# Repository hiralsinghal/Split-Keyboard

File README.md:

# Split-Keyboard
A split-keyboard made for ergnomic comfort. It has 42 keys, each side having 21. XIAO-nRF5280 is the MCU powering the project because of its wireless support.

## Features

- Wireless
- XIAO-nRF52840 is the MCU.
- 42 keys

## Schematic

You have draw hierarchical sheets and set the sheetname respectly whereas the sheet file should be named the same for both so that whatever symbols you place in one of them are copied into the other without you switching sheets constantly. This wouldnt impact the way footprints are imported into the PCB editor.

### Left Side

### Right Side

## PCB

The source files are in the PCB folder.

## Case

This was made in Fusion, using the PCB as reference. It has cutouts for switches, keys and XIAO ports. The source file can be found in the folder CAD.

### Left

This is the case for the left side of the keyboard.

### Right

This is the case for the right side of the keyboard.

## Firmware

It uses ZMK firmware because of its support for split keyboards. Each controller runs their own firmware but they make it work as a single device. The files are in the firmware folder.

## BOM

| Item | Description | Quantity | Unit Price ($) | Total Price ($) | URL |
| --- | --- |---| --- |--- | --- |
| PCB | PCB | 5 | 3.32 | 16.6 | |
| Seeed Studio XIAO BLE nRF52840 |MCU |2|12.2|24.4|https://robu.in/product/seeed-studio-xiao-ble-nrf52840/ |
| Akko V3 Lavender Purple Pro Switch (Pack of 45)| Keyboard Switches | 1 | 11.65 | 11.65 | https://stackskb.com/store/akko-v3-lavender-purple-pro-switch-pack-of-45/ |
| Veekos Gradient Keycaps (Cherry Profile) (135 keys)| Keycaps | 1 | 13.77 | 13.77 | https://stackskb.com/store/veekos-gradient-keycaps-cherry-profile-135-keys/?attribute_pa_colour=black |
| 1N5819 1W Diode | Diode | 42 | 0.027 | 1.13 | https://robu.in/product/1n5819-1w-diode-pack-of-30/ |
| 0805S8F1005T5E-Royal Ohm-10M 1% 0805 SMD Resistor | Resistor | 4 | 0.0086 | 0.034 | https://robu.in/product/0805s8f1005t5e-royal-ohm-10m-1-0805-smd-resistor/
| Total | | | |67.584| |

## Zine

This was made in Figma. I enjoyed making it kinda.

## Why did I make it?

I made it cause it seemed like a cool project. The routing was tough ngl. Each footprint alligned differently and so many switches and diodes. Its like each project is improving my skills consistently. I now know how to route better (kinda) This was made for [Fallout](fallout.hackclub.com).

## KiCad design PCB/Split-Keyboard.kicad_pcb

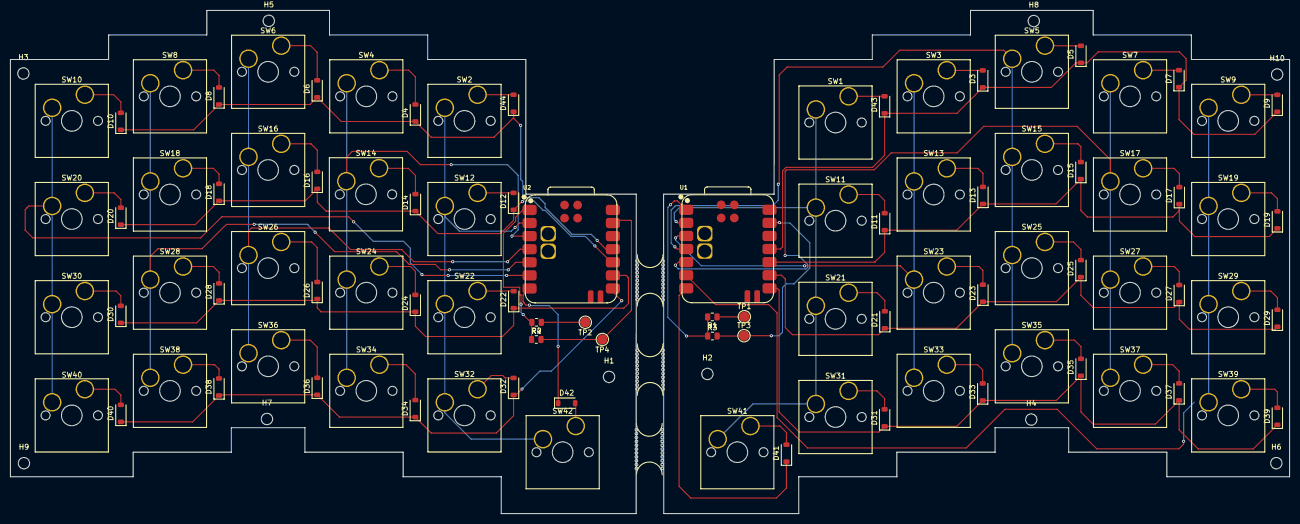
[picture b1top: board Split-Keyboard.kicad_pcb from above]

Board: 2 copper layers, 248.2 x 97.6 mm, 107 parts (0 on the bottom side), 67 nets.

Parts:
B01, B02, B03: break off; mouse-bite-5mm-slot
D3, D4, D5, D6, D7, D8, D9, D10, D11, D12, D13, D14, D15, D16, D17, D18, D19, D20, D21, D22, D23, D24, D25, D26, D27, D28, D29, D30, D31, D32, D33, D34, D35, D36, D37, D38, D39, D40, D41, D42, D43, D44: D; D_SOD-123
H1, H2, H3, H4, H5, H6, H7, H8, H9, H10: MountingHole; MountingHole_2.2mm_M2
R1, R2: 806k; R_0805_2012Metric
R3, R4: 2M; R_0805_2012Metric
SW1, SW2, SW3, SW4, SW5, SW6, SW7, SW8, SW9, SW10, SW11, SW12, SW13, SW14, SW15, SW16, SW17, SW18, SW19, SW20, SW21, SW22, SW23, SW24, SW25, SW26, SW27, SW28, SW29, SW30, SW31, SW32, SW33, SW34, SW35, SW36, SW37, SW38, SW39, SW40, SW41, SW42: SW_Push; SW_Hotswap_Kailh_MX_Plated_1.00u_With_Switch
TP1, TP2, TP3, TP4: TestPoint; TestPoint_Pad_D2.0mm
U1, U2: XIAO-nRF52840-SMD; modified-XIAO-nRF52840-SMD

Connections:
/left/BT_PIN: R1.2, R3.1, U1.1 (P0.02_A0_D0)
/left/COL0: SW1.1, SW11.1, SW21.1, SW31.1, SW41.1, U1.2 (P0.03_A1_D1)
/left/COL1: SW3.1, SW13.1, SW23.1, SW33.1, U1.3 (P0.28_A2_D2)
/left/COL2: SW5.1, SW15.1, SW25.1, SW35.1, U1.4 (P0.29_A3_D3)
/left/COL3: SW7.1, SW17.1, SW27.1, SW37.1, U1.5 (P0.04_A4_D4_SDA)
/left/COL4: SW9.1, SW19.1, SW29.1, SW39.1, U1.6 (P0.05_A5_D5_SCL)
/left/ROW0: D3.1 (K), D5.1 (K), D7.1 (K), D9.1 (K), D43.1 (K), U1.11 (P1.15_D10_MOSI)
/left/ROW1: D11.1 (K), D13.1 (K), D15.1 (K), D17.1 (K), D19.1 (K), U1.10 (P1.14_D9_MISO)
/left/ROW2: D21.1 (K), D23.1 (K), D25.1 (K), D27.1 (K), D29.1 (K), U1.9 (P1.13_D8_SCK)
/left/ROW3: D31.1 (K), D33.1 (K), D35.1 (K), D37.1 (K), D39.1 (K), U1.8 (P1.12_D7_RX)
/left/ROW4: D41.1 (K), U1.7 (P1.11_D6_TX)
/left/VBAT: R1.1, TP1.1 (1_1)
/right/BT_PIN: R2.2, R4.1, U2.1 (P0.02_A0_D0)
/right/COL0: SW2.1, SW12.1, SW22.1, SW32.1, SW42.1, U2.2 (P0.03_A1_D1)
/right/COL1: SW4.1, SW14.1, SW24.1, SW34.1, U2.3 (P0.28_A2_D2)
/right/COL2: SW6.1, SW16.1, SW26.1, SW36.1, U2.4 (P0.29_A3_D3)
/right/COL3: SW8.1, SW18.1, SW28.1, SW38.1, U2.5 (P0.04_A4_D4_SDA)
/right/COL4: SW10.1, SW20.1, SW30.1, SW40.1, U2.6 (P0.05_A5_D5_SCL)
/right/ROW0: D4.1 (K), D6.1 (K), D8.1 (K), D10.1 (K), D44.1 (K), U2.11 (P1.15_D10_MOSI)
/right/ROW1: D12.1 (K), D14.1 (K), D16.1 (K), D18.1 (K), D20.1 (K), U2.10 (P1.14_D9_MISO)
/right/ROW2: D22.1 (K), D24.1 (K), D26.1 (K), D28.1 (K), D30.1 (K), U2.9 (P1.13_D8_SCK)
/right/ROW3: D32.1 (K), D34.1 (K), D36.1 (K), D38.1 (K), D40.1 (K), U2.8 (P1.12_D7_RX)
/right/ROW4: D42.1 (K), U2.7 (P1.11_D6_TX)
/right/VBAT: R2.1, TP2.1 (1_1)
GND: R3.2, R4.2, TP3.1 (1_1), TP4.1 (1_1), U1.13 (GND), U2.13 (GND)
unnamed: D3.2 (A), SW3.2
unnamed: D4.2 (A), SW4.2
unnamed: D5.2 (A), SW5.2
unnamed: D6.2 (A), SW6.2
unnamed: D7.2 (A), SW7.2
unnamed: D8.2 (A), SW8.2
unnamed: D9.2 (A), SW9.2
unnamed: D10.2 (A), SW10.2
unnamed: D11.2 (A), SW11.2
unnamed: D12.2 (A), SW12.2
unnamed: D13.2 (A), SW13.2
unnamed: D14.2 (A), SW14.2
unnamed: D15.2 (A), SW15.2
unnamed: D16.2 (A), SW16.2
unnamed: D17.2 (A), SW17.2
unnamed: D18.2 (A), SW18.2
unnamed: D19.2 (A), SW19.2
unnamed: D20.2 (A), SW20.2
unnamed: D21.2 (A), SW21.2
unnamed: D22.2 (A), SW22.2
unnamed: D23.2 (A), SW23.2
unnamed: D24.2 (A), SW24.2
unnamed: D25.2 (A), SW25.2
unnamed: D26.2 (A), SW26.2
unnamed: D27.2 (A), SW27.2
unnamed: D28.2 (A), SW28.2
unnamed: D29.2 (A), SW29.2
unnamed: D30.2 (A), SW30.2
unnamed: D31.2 (A), SW31.2
unnamed: D32.2 (A), SW32.2
unnamed: D33.2 (A), SW33.2
unnamed: D34.2 (A), SW34.2
unnamed: D35.2 (A), SW35.2
unnamed: D36.2 (A), SW36.2
unnamed: D37.2 (A), SW37.2
unnamed: D38.2 (A), SW38.2
unnamed: D39.2 (A), SW39.2
unnamed: D40.2 (A), SW40.2
unnamed: D41.2 (A), SW41.2
unnamed: D42.2 (A), SW42.2
unnamed: D43.2 (A), SW1.2
unnamed: D44.2 (A), SW2.2

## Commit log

2026-06-15 initial
2026-06-20 pcb stuff
2026-06-20 bom & cad things
2026-06-20 zine update
2026-06-20 readme update
2026-06-20 firmware added
2026-06-20 firmware
2026-06-20 bom updates
2026-06-24 fix case img
2026-06-24 update bom
2026-06-24 add case step
